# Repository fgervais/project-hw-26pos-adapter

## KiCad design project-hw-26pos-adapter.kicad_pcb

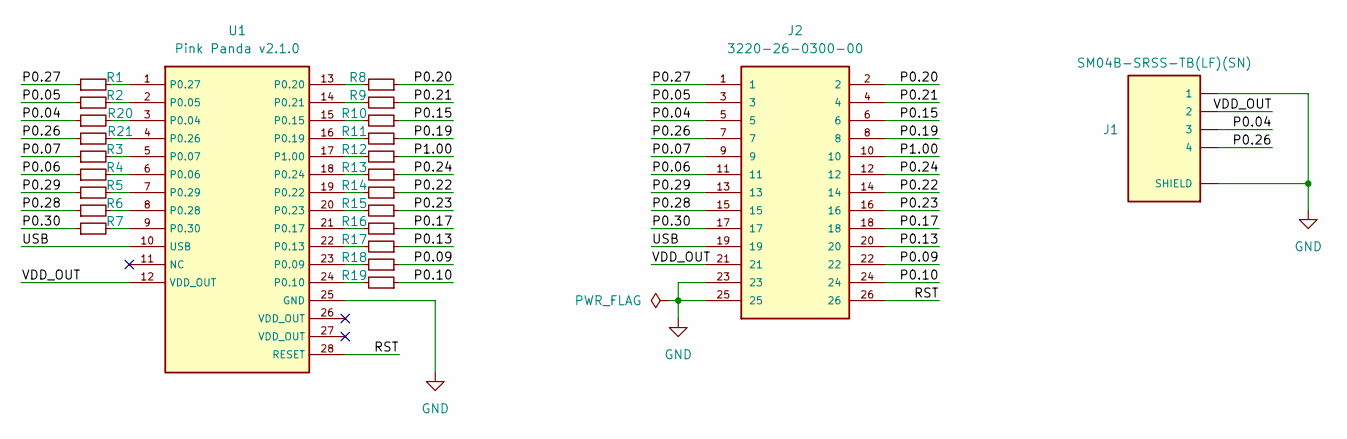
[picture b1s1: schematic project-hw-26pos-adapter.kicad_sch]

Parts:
J1: SM04B-SRSS-TB(LF)(SN); JST_SM04B-SRSS-TB(LF)(SN)
J2: 3220-26-0300-00; CNC_3220-26-0300-00; PARTREV A
R1, R2, R3, R4, R5, R6, R7, R8, R9, R10, R11, R12, R13, R14, R15, R16, R17, R18, R19, R20, R21: R_Small; R_0603_1608Metric
U1: Pink Panda v2.1.0; pink_panda_SMD

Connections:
/P0.04: J1.3, J2.5, R20.1
/P0.05: J2.3, R2.1
/P0.06: J2.11, R4.1
/P0.07: J2.9, R3.1
/P0.09: J2.22, R18.1
/P0.10: J2.24, R19.1
/P0.13: J2.20, R17.1
/P0.15: J2.6, R10.1
/P0.17: J2.18, R16.1
/P0.19: J2.8, R11.1
/P0.20: J2.2, R8.1
/P0.21: J2.4, R9.1
/P0.22: J2.14, R14.1
/P0.23: J2.16, R15.1
/P0.24: J2.12, R13.1
/P0.26: J1.4, J2.7, R21.1
/P0.27: J2.1, R1.1
/P0.28: J2.15, R6.1
/P0.29: J2.13, R5.1
/P0.30: J2.17, R7.1
/P1.00: J2.10, R12.1
/RST: J2.26, U1.28 (RESET)
/USB: J2.19, U1.10 (USB)
/VDD_OUT: J1.2, J2.21, U1.12 (VDD_OUT)
GND: J1.1, J1.S1 (SHIELD), J1.S2 (SHIELD), J2.23, J2.25, U1.25 (GND)
unnamed: R20.2, U1.3 (P0.04)
unnamed: R2.2, U1.2 (P0.05)
unnamed: R4.2, U1.6 (P0.06)
unnamed: R3.2, U1.5 (P0.07)
unnamed: R18.2, U1.23 (P0.09)
unnamed: R19.2, U1.24 (P0.10)
unnamed: R17.2, U1.22 (P0.13)
unnamed: R10.2, U1.15 (P0.15)
unnamed: R16.2, U1.21 (P0.17)
unnamed: R11.2, U1.16 (P0.19)
unnamed: R8.2, U1.13 (P0.20)
unnamed: R9.2, U1.14 (P0.21)
unnamed: R14.2, U1.19 (P0.22)
unnamed: R15.2, U1.20 (P0.23)
unnamed: R13.2, U1.18 (P0.24)
unnamed: R21.2, U1.4 (P0.26)
unnamed: R1.2, U1.1 (P0.27)
unnamed: R6.2, U1.8 (P0.28)
unnamed: R5.2, U1.7 (P0.29)
unnamed: R7.2, U1.9 (P0.30)
unnamed: R12.2, U1.17 (P1.00)

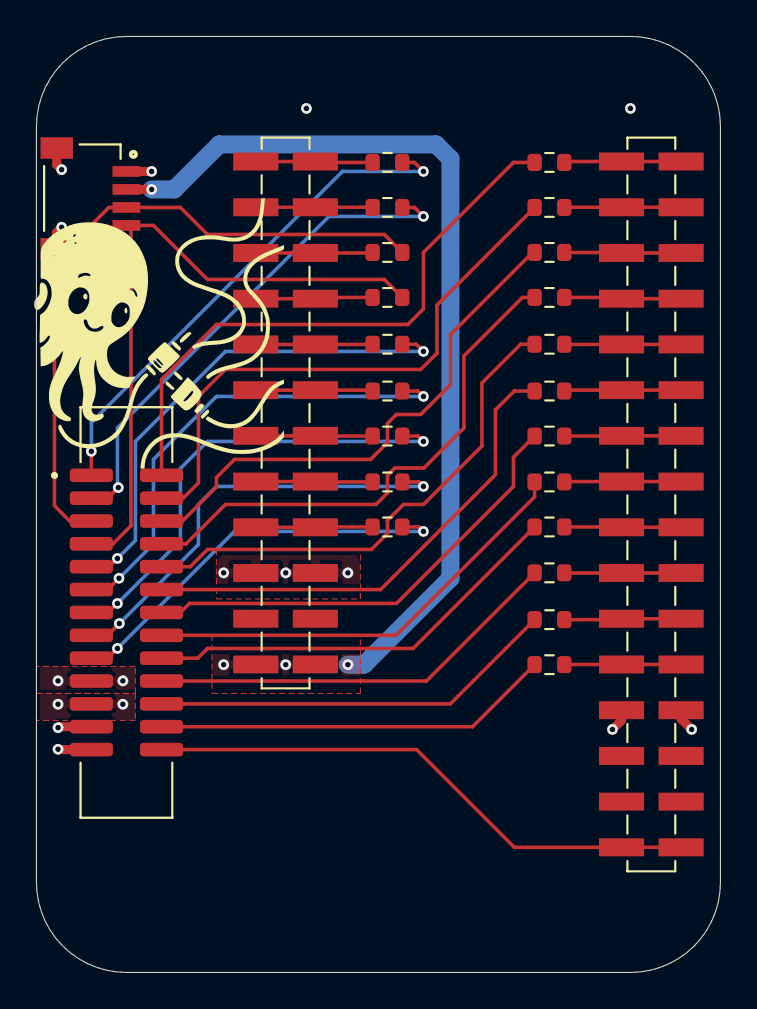
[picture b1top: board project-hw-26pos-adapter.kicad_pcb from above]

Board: 4 copper layers, 38.0 x 52.0 mm, 24 parts (0 on the bottom side), 46 nets.

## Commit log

2025-05-15 sch: add symbols
2025-05-17 sch: add connections
2025-05-18 pcb: first rough routing
2025-05-18 pcb: complete routing
2025-05-19 Print 1:1
2025-05-19 pcb: add version on board
2025-05-27 Add series resistors
2025-05-27 pcb: update version on silkscreen
2025-05-28 Also add series resistors to SDA/SCL
2025-05-28 pcb: add a few ground vias
